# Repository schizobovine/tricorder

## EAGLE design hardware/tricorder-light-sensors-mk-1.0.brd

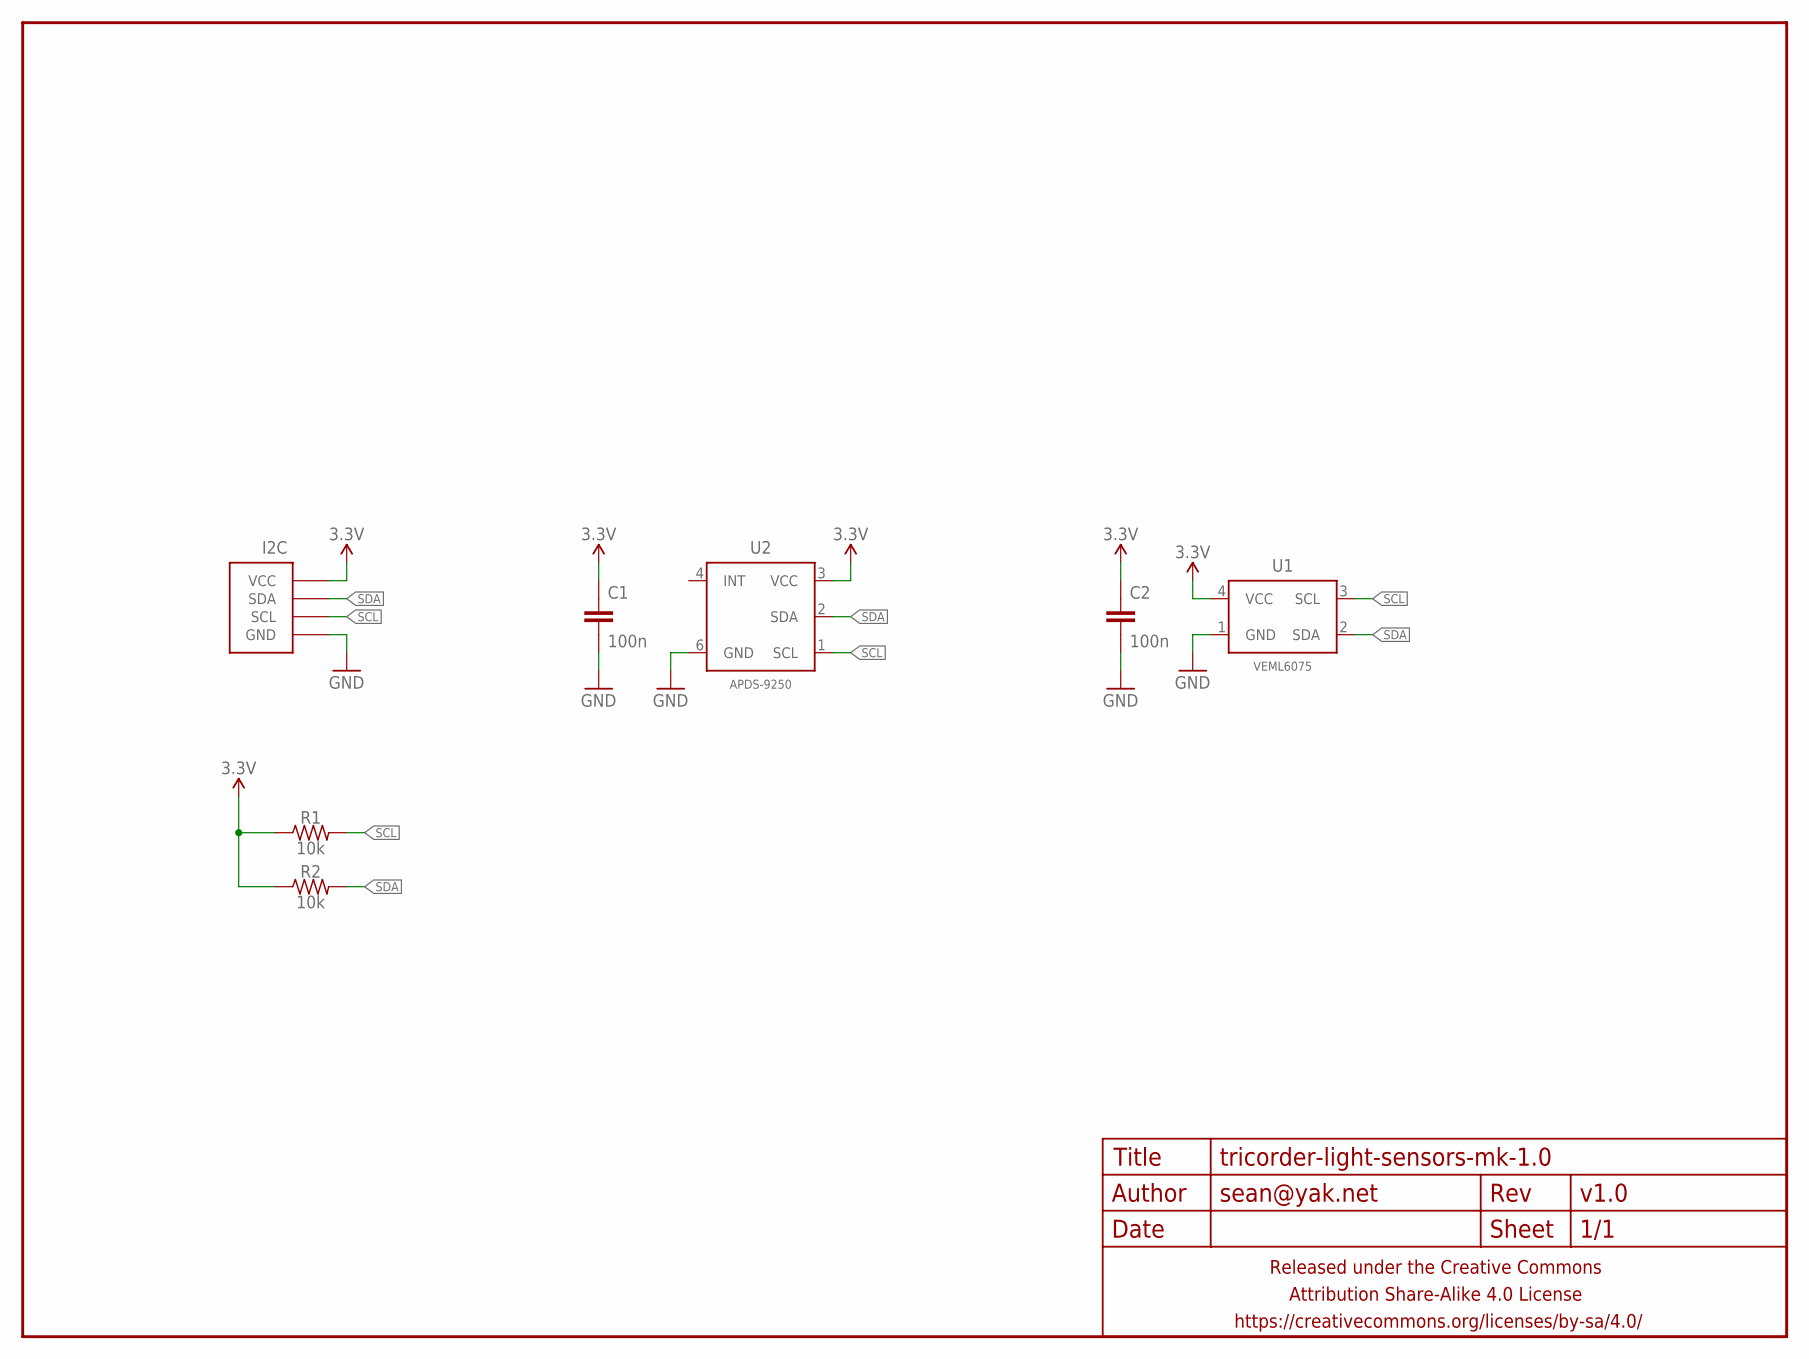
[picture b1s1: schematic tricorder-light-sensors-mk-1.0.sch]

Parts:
C1, C2: 100n; C0603
FRAME1: FRAME-LETTERNO_PACKAGE; DUMMY
I2C: M04-I2CPTH-0.1IN-CENTERED; 1X04-PTH-VERT-I2C-CENTERED
R1, R2: 10k; R0603
U1: VEML6075; OPLGA4
U2: APDS-9250; APDS-9250-ALT

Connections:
3.3V: C1.1, C2.1, I2C.VCC, R1.1, R2.1, U1.4 (VCC), U2.3 (VCC)
GND: C1.2, C2.2, I2C.GND, U1.1 (GND), U2.6 (GND)
SCL: I2C.SCL, R1.2, U1.3 (SCL), U2.1 (SCL)
SDA: I2C.SDA, R2.2, U1.2 (SDA), U2.2 (SDA)

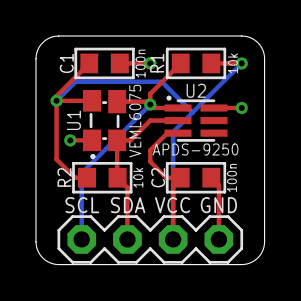
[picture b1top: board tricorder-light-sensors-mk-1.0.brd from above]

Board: 2 copper layers, 12.7 x 12.7 mm, 8 parts (0 on the bottom side), 4 nets.

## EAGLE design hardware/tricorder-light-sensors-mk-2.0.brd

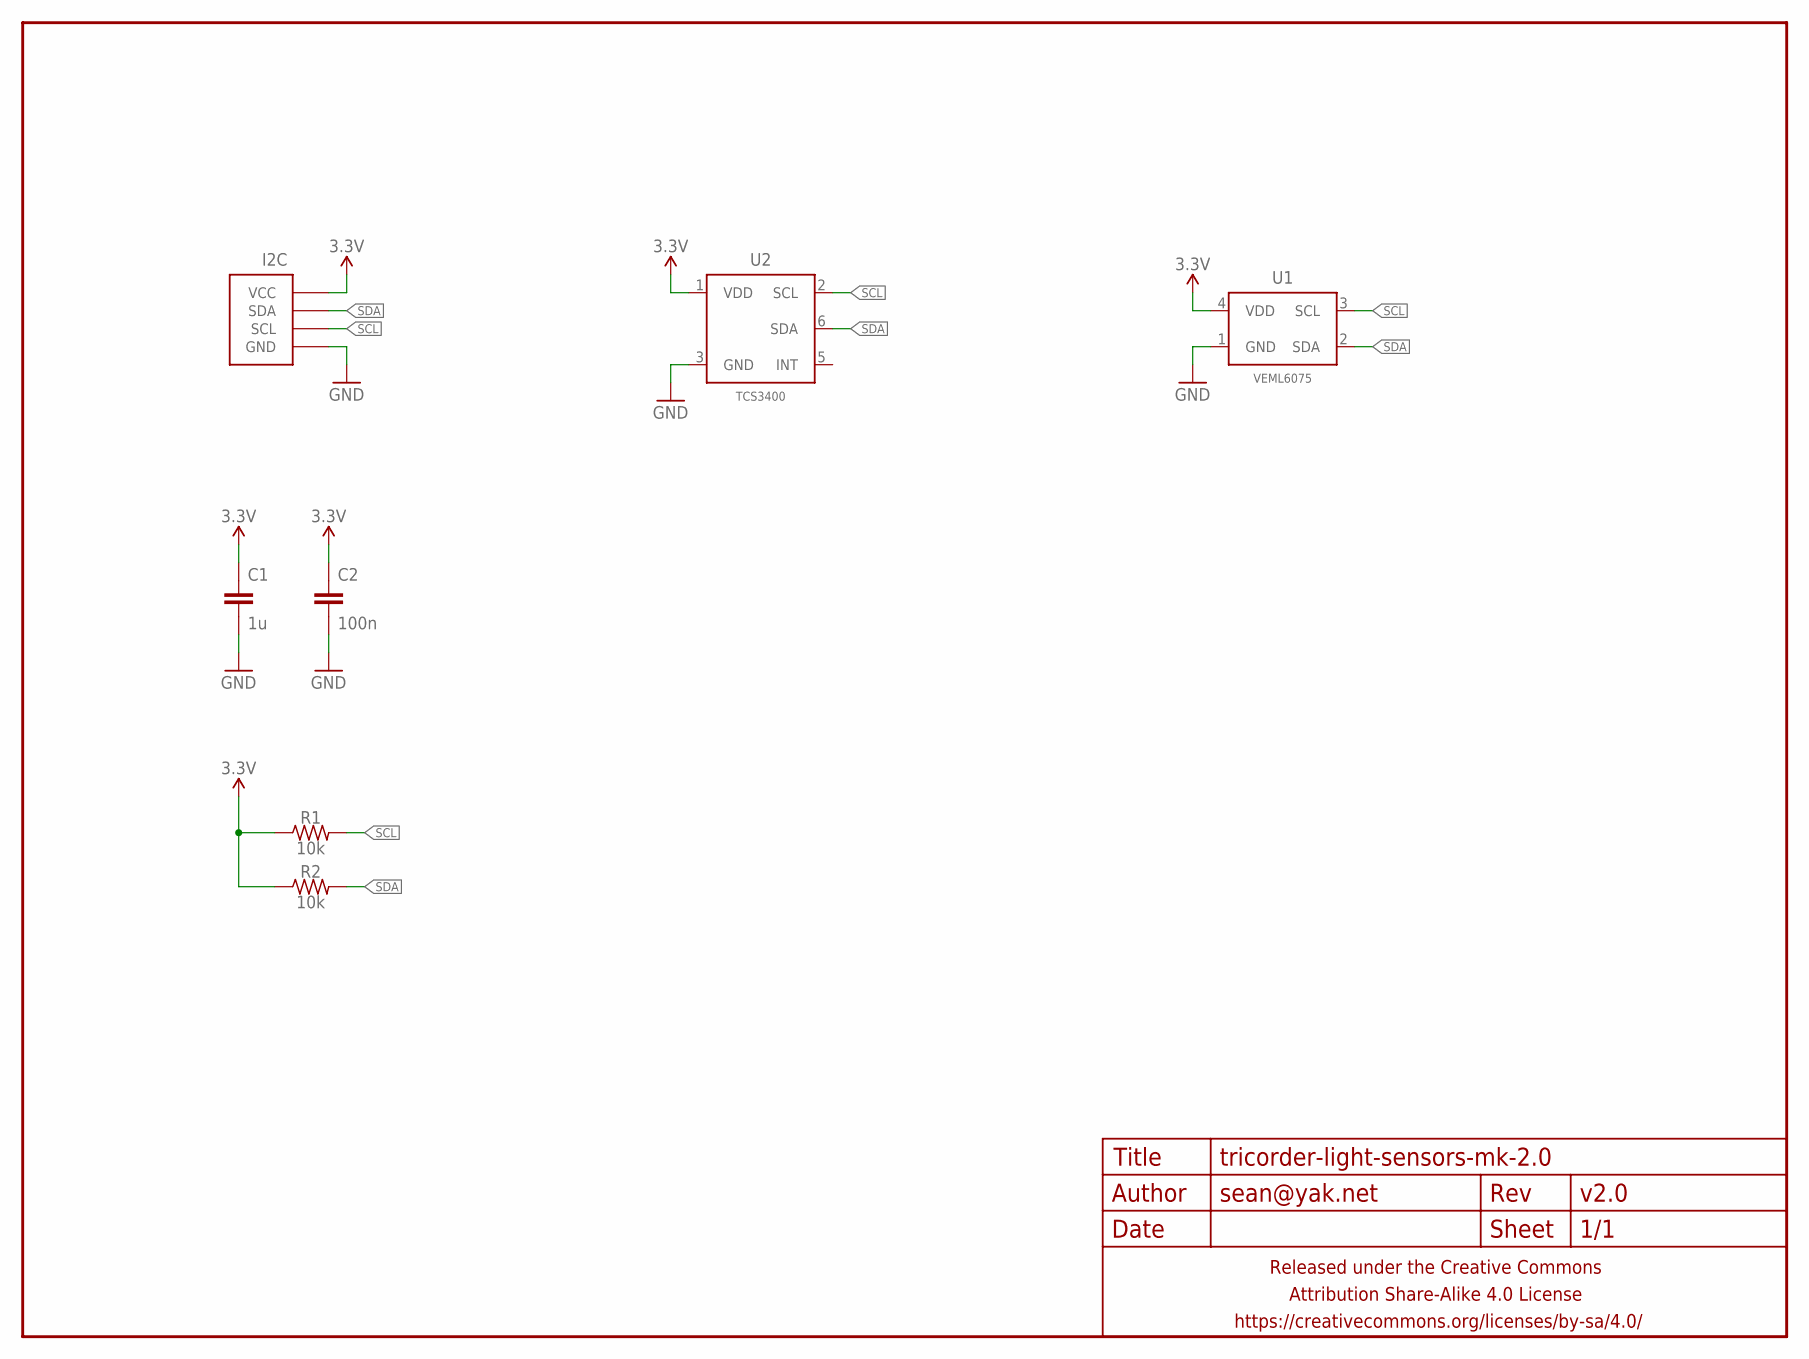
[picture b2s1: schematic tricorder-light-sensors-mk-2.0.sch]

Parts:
C1: 1u; C0603
C2: 100n; C0603
FRAME1: FRAME-LETTERNO_PACKAGE; DUMMY
I2C: M04-I2CPTH-0.1IN-CENTERED; 1X04-PTH-VERT-I2C-CENTERED
R1, R2: 10k; R0603
U1: VEML6075; OPLGA4
U2: TCS3400; TCS3400_DFN6

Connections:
3.3V: C1.1, C2.1, I2C.VCC, R1.1, R2.1, U1.4 (VDD), U2.1 (VDD)
GND: C1.2, C2.2, I2C.GND, U1.1 (GND), U2.3 (GND)
SCL: I2C.SCL, R1.2, U1.3 (SCL), U2.2 (SCL)
SDA: I2C.SDA, R2.2, U1.2 (SDA), U2.6 (SDA)

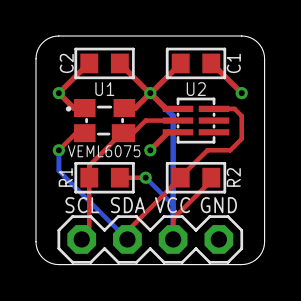
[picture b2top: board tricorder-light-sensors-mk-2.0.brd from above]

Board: 2 copper layers, 12.7 x 12.7 mm, 8 parts (0 on the bottom side), 4 nets.

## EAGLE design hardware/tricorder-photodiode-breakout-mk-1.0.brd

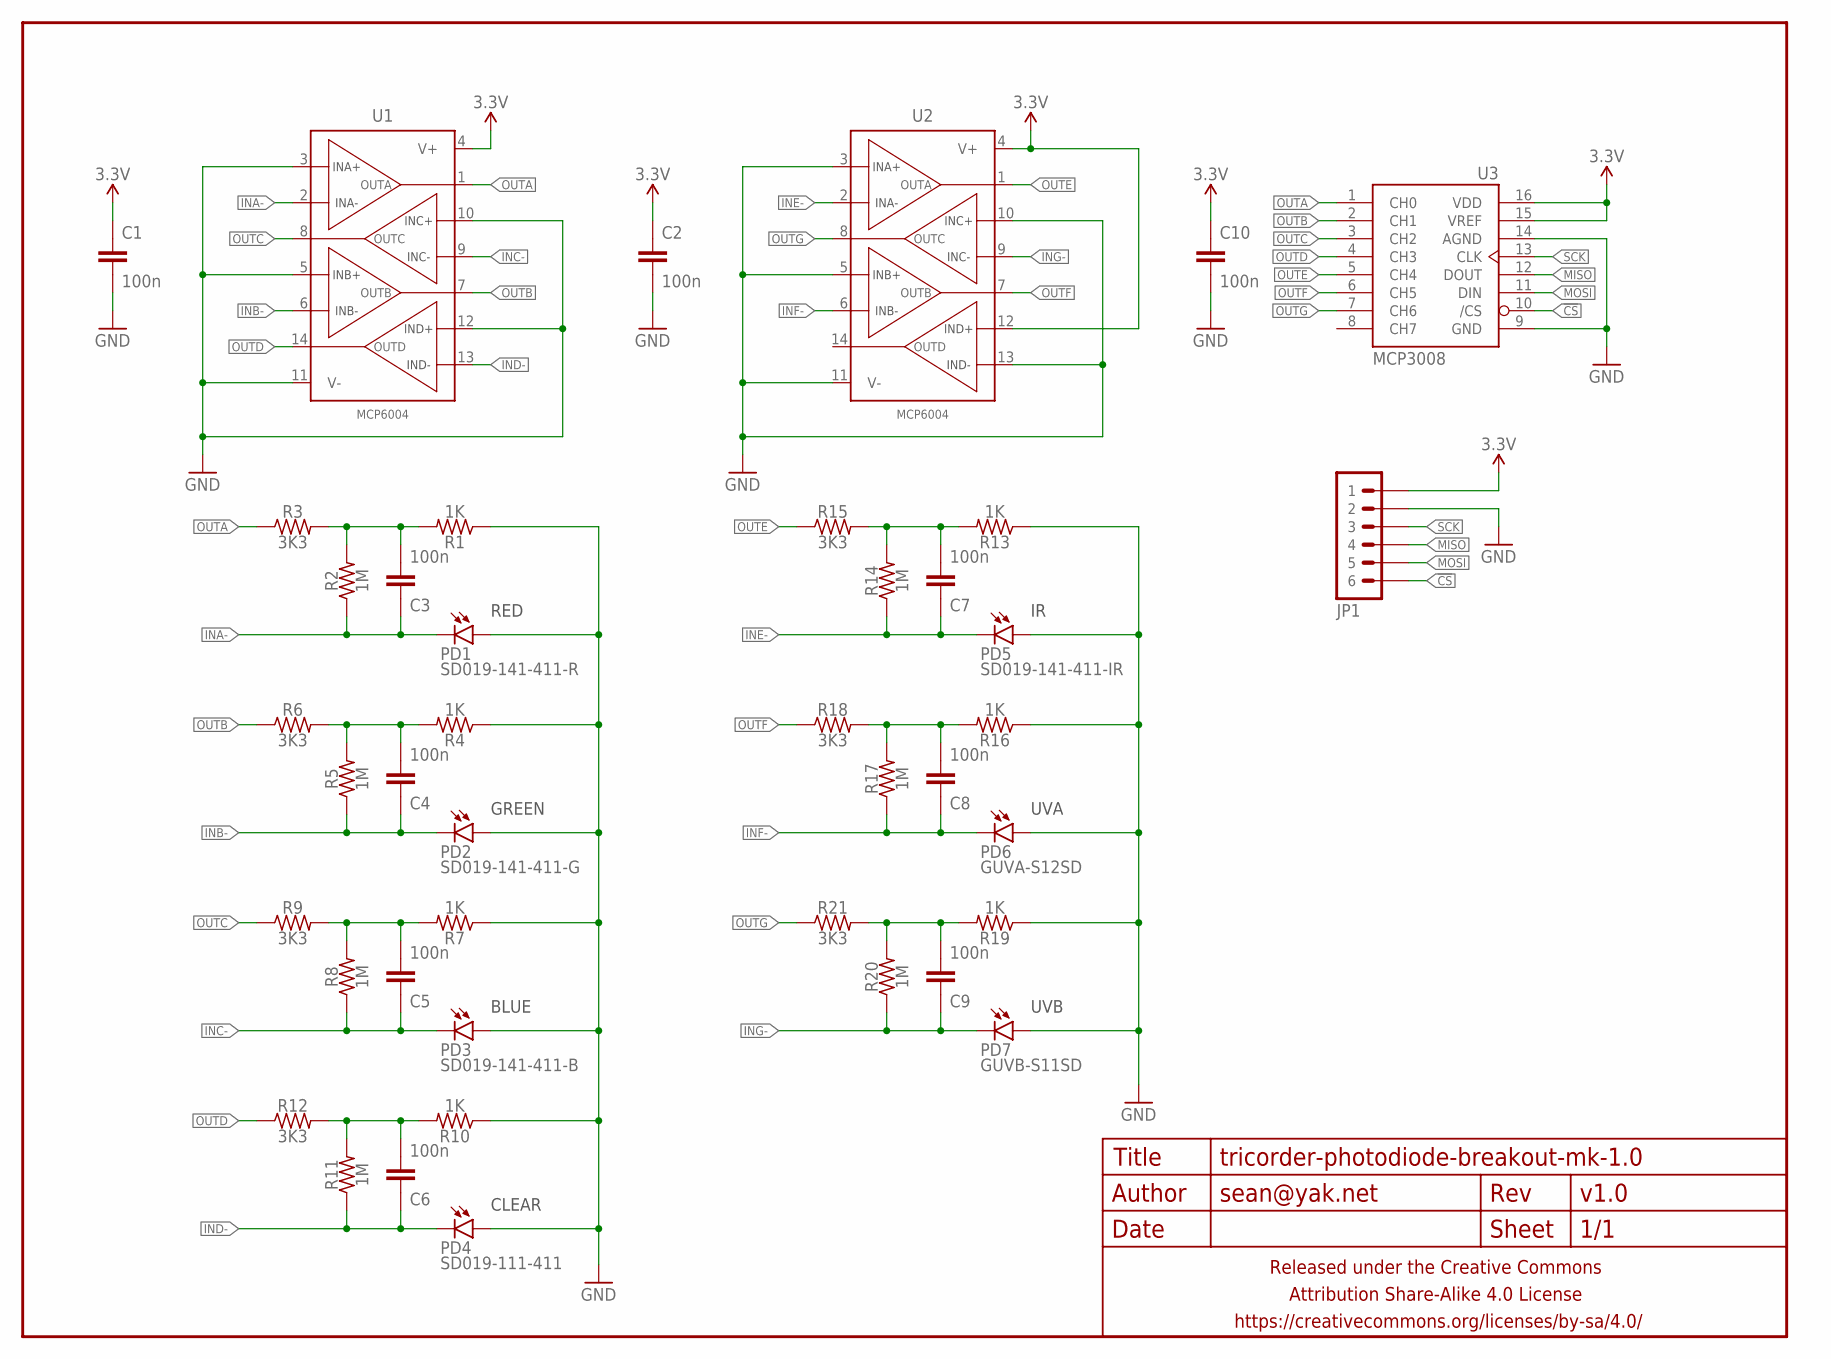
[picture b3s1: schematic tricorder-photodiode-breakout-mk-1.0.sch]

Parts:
C1, C2, C3, C4, C5, C6, C7, C8, C9, C10: 100n; C0603
FRAME1: FRAME-LETTERNO_PACKAGE; DUMMY
JP1: M06JST-PH-PTH-VERT; JST-6-PH-VERT-PTH
PD1: SD019-141-411-R; LED-0805
PD2: SD019-141-411-G; LED-0805
PD3: SD019-141-411-B; LED-0805
PD4: SD019-111-411; LED-0805
PD5: SD019-141-411-IR; LED-0805
PD6: GUVA-S12SD; LED3528
PD7: GUVB-S11SD; LED3528
R1, R4, R7, R10, R13, R16, R19: 1K; R0603
R2, R5, R8, R11, R14, R17, R20: 1M; R0603
R3, R6, R9, R12, R15, R18, R21: 3K3; R0603
U1, U2: MCP6004; SO14
U3: MCP3008; SO16

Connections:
3.3V: C1.1, C2.1, C10.1, JP1.1, U1.4 (V+), U2.4 (V+), U2.12 (IND+), U3.15 (VREF), U3.16 (VDD)
!CS: JP1.6, U3.10 (/CS)
GND: C1.2, C2.2, C10.2, JP1.2, PD1.A, PD2.A, PD3.A, PD4.A, PD5.A, PD6.A, PD7.A, R1.1, R4.1, R7.1, R10.1, R13.1, R16.1, R19.1, U1.3 (INA+), U1.5 (INB+), U1.10 (INC+), U1.11 (V-), U1.12 (IND+), U2.3 (INA+), U2.5 (INB+), U2.10 (INC+), U2.11 (V-), U2.13 (IND-), U3.9 (GND), U3.14 (AGND)
INA-: C3.1, PD1.C, R2.1, U1.2 (INA-)
INB-: C4.1, PD2.C, R5.1, U1.6 (INB-)
INC-: C5.1, PD3.C, R8.1, U1.9 (INC-)
IND-: C6.1, PD4.C, R11.1, U1.13 (IND-)
INE-: C7.1, PD5.C, R14.1, U2.2 (INA-)
INF-: C8.1, PD6.K (C), R17.1, U2.6 (INB-)
ING-: C9.1, PD7.K (C), R20.1, U2.9 (INC-)
MISO: JP1.4, U3.12 (DOUT)
MOSI: JP1.5, U3.11 (DIN)
unnamed: C3.2, R1.2, R2.2, R3.2
unnamed: C4.2, R4.2, R5.2, R6.2
unnamed: C5.2, R7.2, R8.2, R9.2
unnamed: C6.2, R10.2, R11.2, R12.2
unnamed: C9.2, R19.2, R20.2, R21.2
unnamed: C7.2, R13.2, R14.2, R15.2
unnamed: C8.2, R16.2, R17.2, R18.2
OUTA: R3.1, U1.1 (OUTA), U3.1 (CH0)
OUTB: R6.1, U1.7 (OUTB), U3.2 (CH1)
OUTC: R9.1, U1.8 (OUTC), U3.3 (CH2)
OUTD: R12.1, U1.14 (OUTD), U3.4 (CH3)
OUTE: R15.1, U2.1 (OUTA), U3.5 (CH4)
OUTF: R18.1, U2.7 (OUTB), U3.6 (CH5)
OUTG: R21.1, U2.8 (OUTC), U3.7 (CH6)
SCK: JP1.3, U3.13 (CLK)

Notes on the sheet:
RED
GREEN
BLUE
CLEAR
UVA
UVB

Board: 2 copper layers, 43 parts (35 on the bottom side), 27 nets, no tracks yet.

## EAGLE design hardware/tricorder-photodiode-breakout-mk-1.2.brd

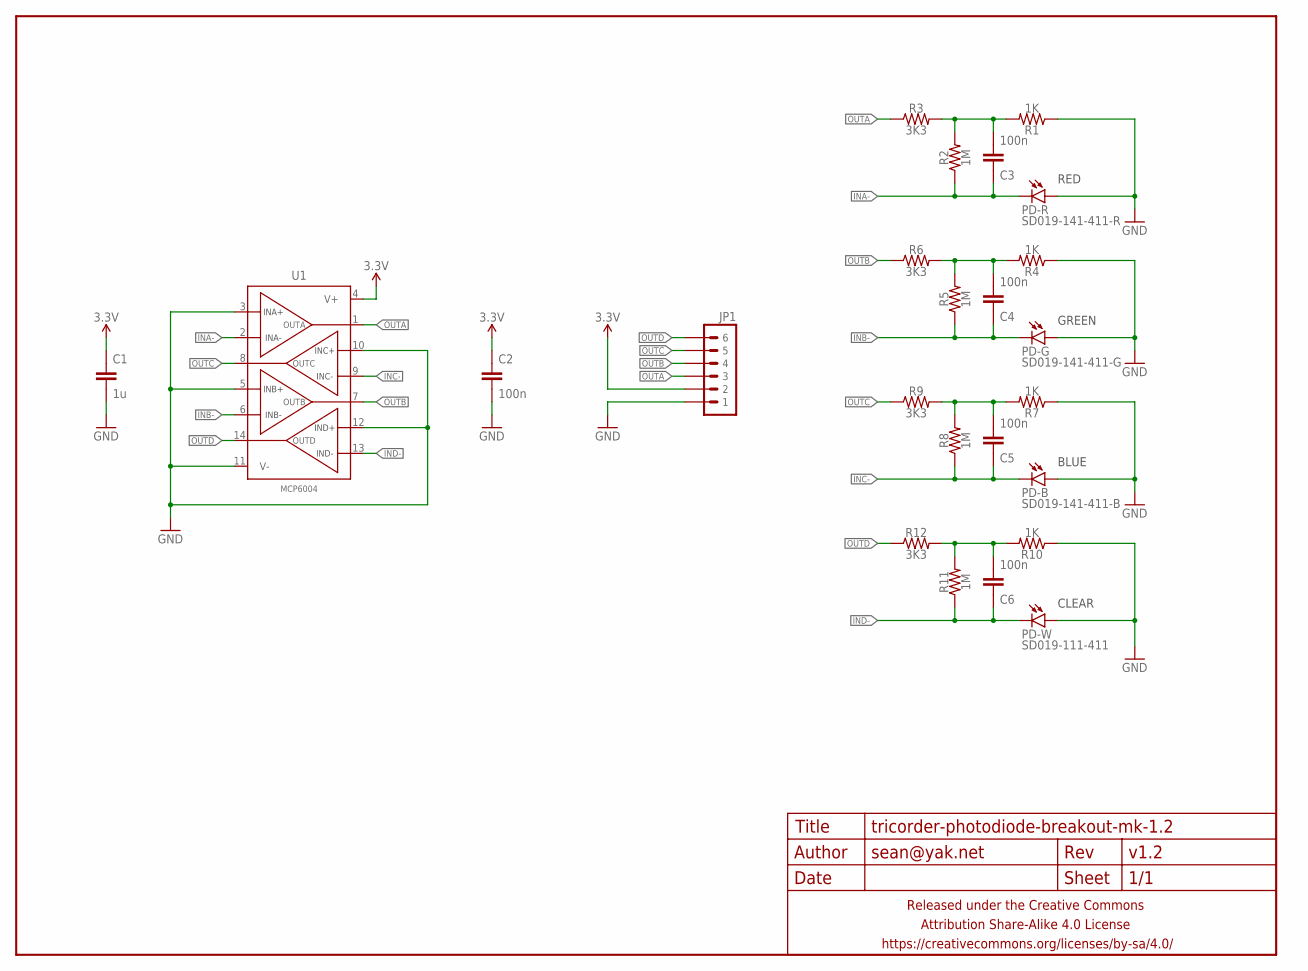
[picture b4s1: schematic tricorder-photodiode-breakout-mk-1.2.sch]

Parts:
C1: 1u; C0603
C2, C3, C4, C5, C6: 100n; C0603
FRAME1: FRAME-LETTERNO_PACKAGE; DUMMY
JP1: M06PTH_CENTERED; 1X06_CENTERED
PD-B: SD019-141-411-B; LED-0805
PD-G: SD019-141-411-G; LED-0805
PD-R: SD019-141-411-R; LED-0805
PD-W: SD019-111-411; LED-0805
R1, R4, R7, R10: 1K; R0603
R2, R5, R8, R11: 1M; R0603
R3, R6, R9, R12: 3K3; R0603
U1: MCP6004; SO14

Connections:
3.3V: C1.1, C2.1, JP1.2, U1.4 (V+)
GND: C1.2, C2.2, JP1.1, PD-B.A, PD-G.A, PD-R.A, PD-W.A, R1.1, R4.1, R7.1, R10.1, U1.3 (INA+), U1.5 (INB+), U1.10 (INC+), U1.11 (V-), U1.12 (IND+)
INA-: C3.1, PD-R.C, R2.1, U1.2 (INA-)
INB-: C4.1, PD-G.C, R5.1, U1.6 (INB-)
INC-: C5.1, PD-B.C, R8.1, U1.9 (INC-)
IND-: C6.1, PD-W.C, R11.1, U1.13 (IND-)
unnamed: C3.2, R1.2, R2.2, R3.2
unnamed: C4.2, R4.2, R5.2, R6.2
unnamed: C5.2, R7.2, R8.2, R9.2
unnamed: C6.2, R10.2, R11.2, R12.2
OUTA: JP1.3, R3.1, U1.1 (OUTA)
OUTB: JP1.4, R6.1, U1.7 (OUTB)
OUTC: JP1.5, R9.1, U1.8 (OUTC)
OUTD: JP1.6, R12.1, U1.14 (OUTD)

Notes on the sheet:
RED
GREEN
BLUE
CLEAR

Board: 2 copper layers, 25 parts (0 on the bottom side), 14 nets, no tracks yet.

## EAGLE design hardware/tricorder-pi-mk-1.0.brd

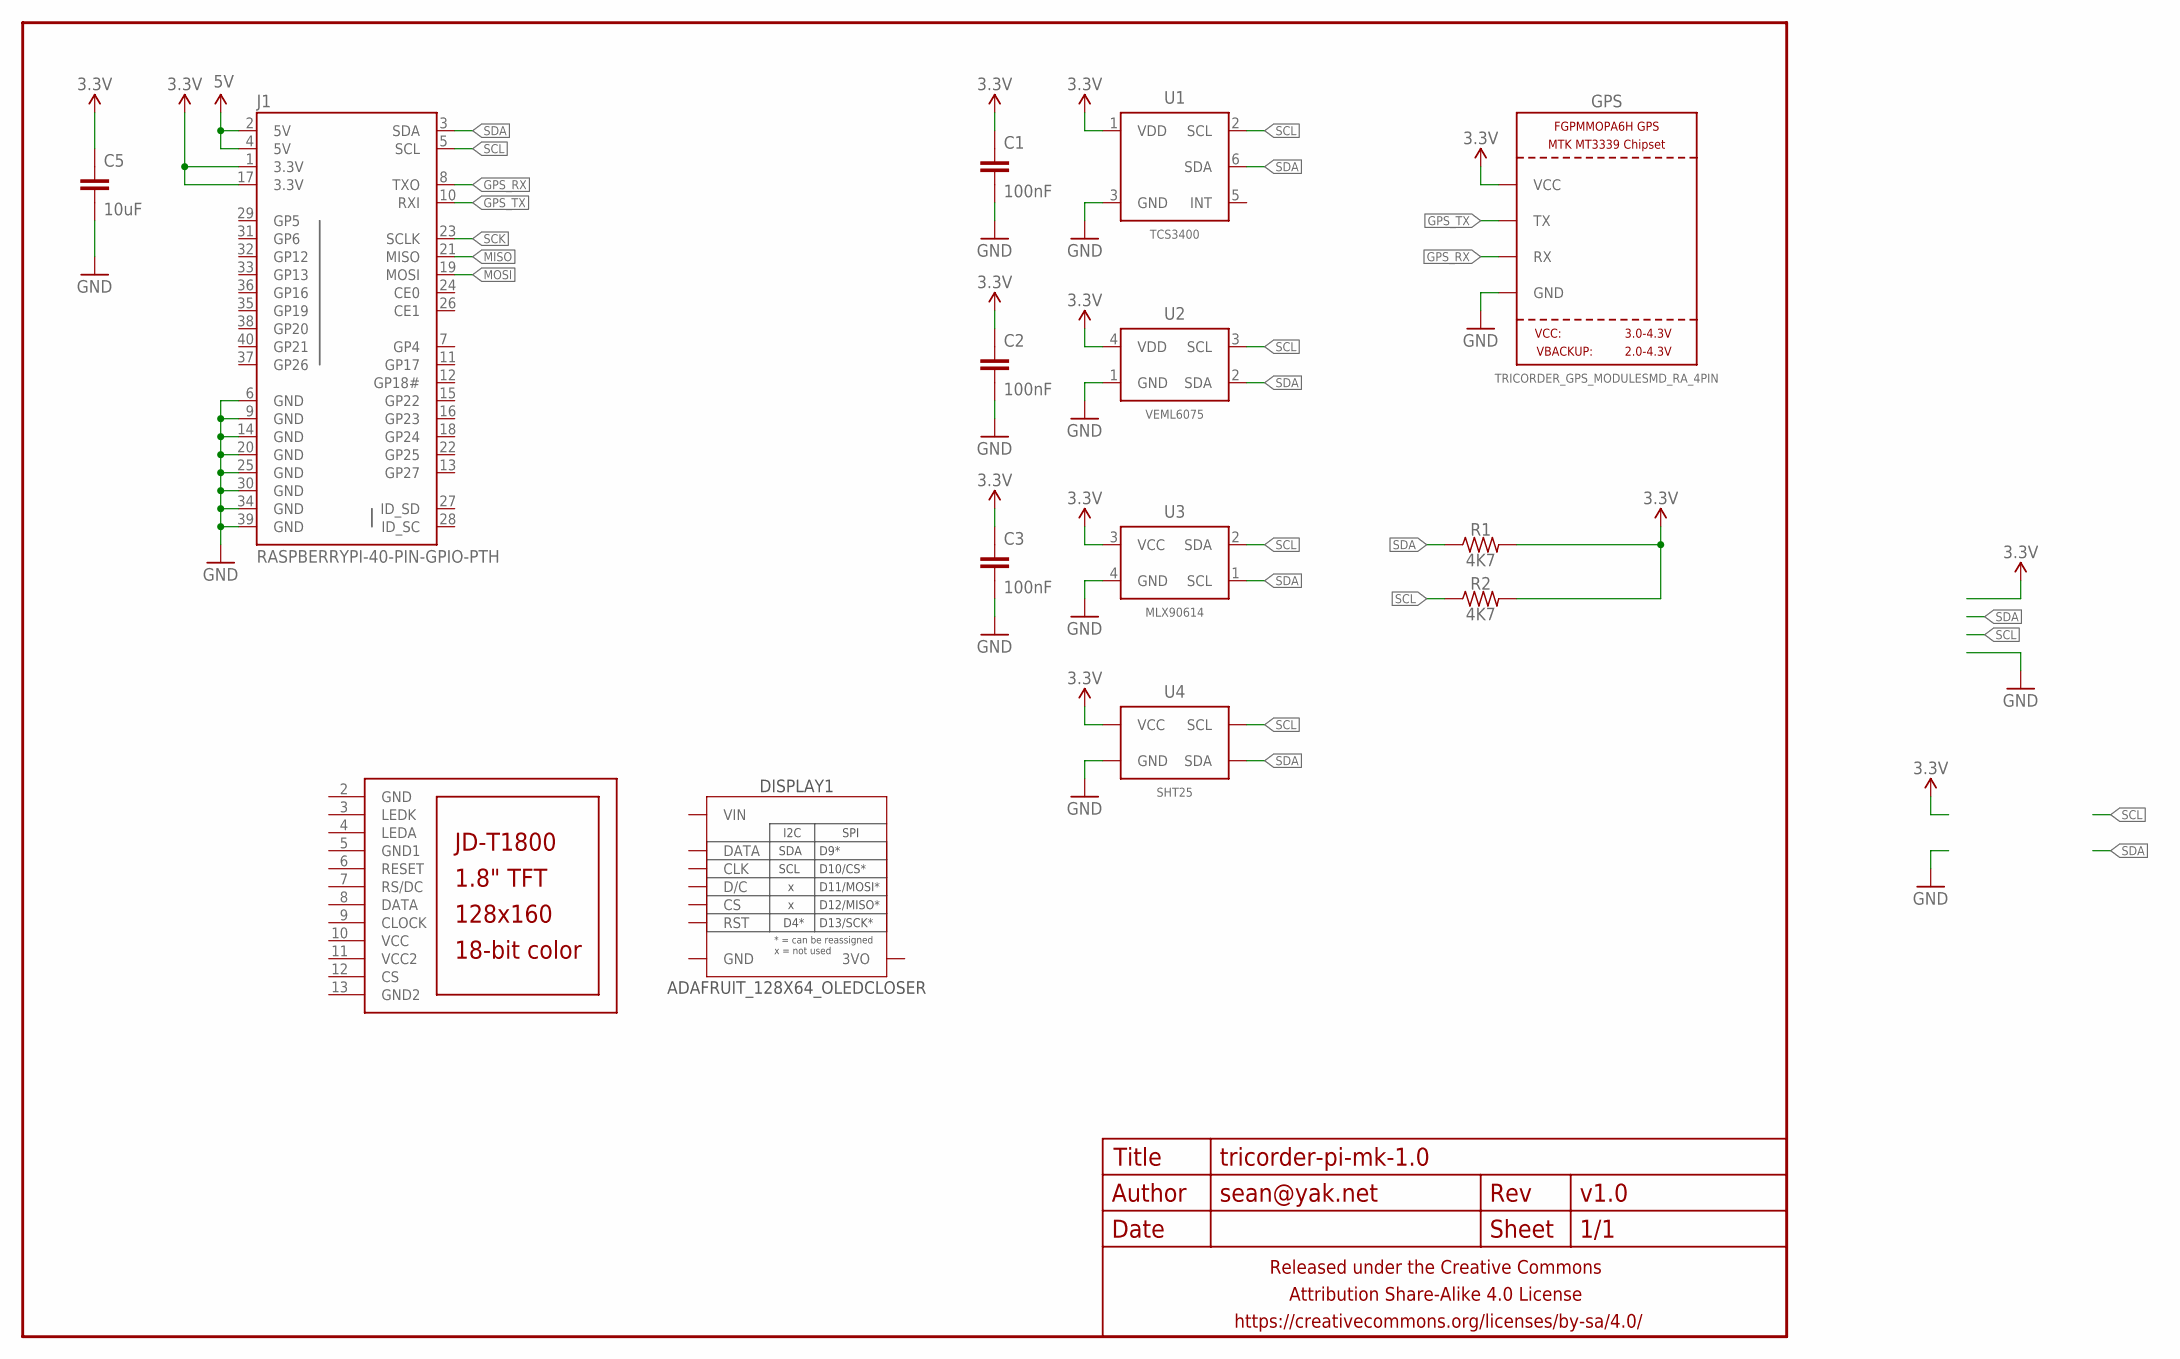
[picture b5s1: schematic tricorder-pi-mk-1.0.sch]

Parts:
C1, C2, C3: 100nF; C0603-TIGHTER
C5: 10uF; C1210
DISPLAY1: ADAFRUIT_128X64_OLEDCLOSER; ADAFRUIT_128X64_OLED_CLOSER
FRAME1: FRAME-LETTERNO_PACKAGE; DUMMY
GPS: TRICORDER_GPS_MODULESMD_RA_4PIN; TRICORDER_GPS_MODULE_RA_CONN_SMD_4PIN
J1: RASPBERRYPI-40-PIN-GPIO-PTH; 2X20_PTH
LCD1: JD-T1800
R1, R2: 4K7; R0603
U1: TCS3400; TCS3400_DFN6
U2: VEML6075; OPLGA4
U3: MLX90614; TO-39-4
U4: SHT25; SHT25_DFN6

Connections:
3.3V: C1.1, C2.1, C3.1, C5.1, GPS.VCC, J1.1 (3.3V), J1.17 (3.3V), R1.2, R2.2, U1.1 (VDD), U2.4 (VDD), U3.3 (VCC), U4.5 (VCC)
5V: J1.2 (5V), J1.4 (5V)
GND: C1.2, C2.2, C3.2, C5.2, GPS.GND, J1.6 (GND), J1.9 (GND), J1.14 (GND), J1.20 (GND), J1.25 (GND), J1.30 (GND), J1.34 (GND), J1.39 (GND), LCD1.2 (GND), U1.3 (GND), U2.1 (GND), U3.4 (GND), U4.2 (GND)
GND1: LCD1.5 (GND1)
GND2: LCD1.13 (GND2)
GPS_RX: GPS.RX, J1.8 (TXO)
GPS_TX: GPS.TX, J1.10 (RXI)
MISO: J1.21 (MISO)
MOSI: J1.19 (MOSI)
SCK: J1.23 (SCLK)
SCL: J1.5 (SCL), R2.1, U1.2 (SCL), U2.3 (SCL), U3.2 (SDA), U4.6 (SCL)
SDA: J1.3 (SDA), R1.1, U1.6 (SDA), U2.2 (SDA), U3.1 (SCL), U4.1 (SDA)
VCC: LCD1.10 (VCC)
VCC2: LCD1.11 (VCC2)

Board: 2 copper layers, 16 parts (3 on the bottom side), 7 nets, no tracks yet.

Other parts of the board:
U$2: COW_SMALL_METAL

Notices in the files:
parts and their libraries:
a_parts: Released under the Creative Commons Attribution Share-Alike 4.0 License
a_parts: https://creativecommons.org/licenses/by-sa/4.0
a_parts: Released under the Creative Commons
